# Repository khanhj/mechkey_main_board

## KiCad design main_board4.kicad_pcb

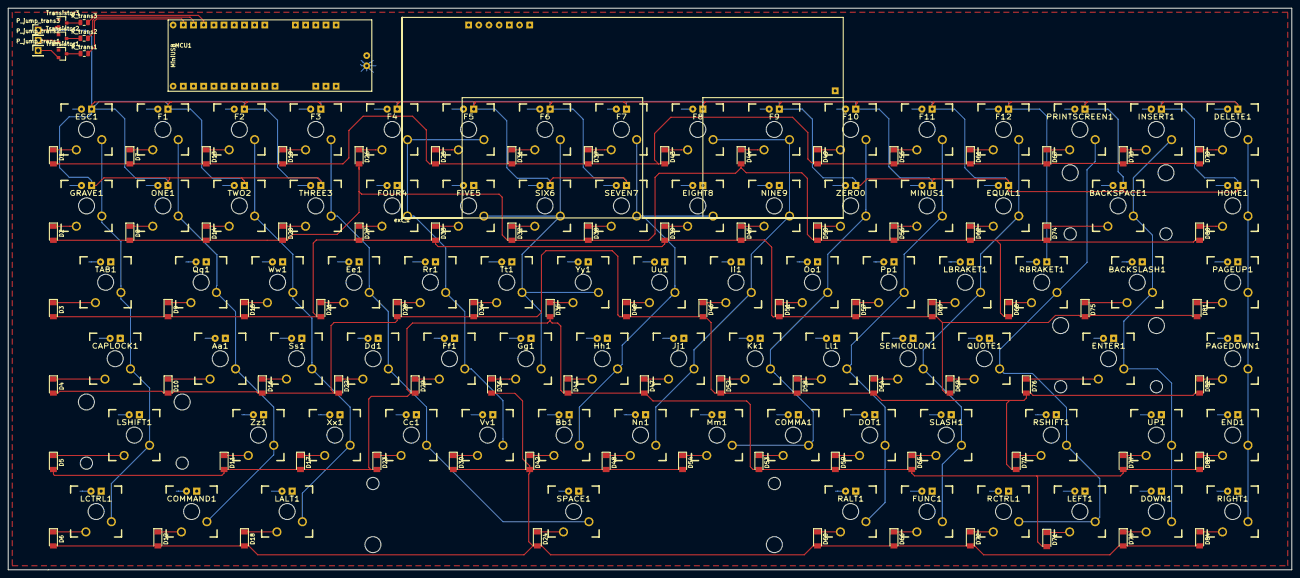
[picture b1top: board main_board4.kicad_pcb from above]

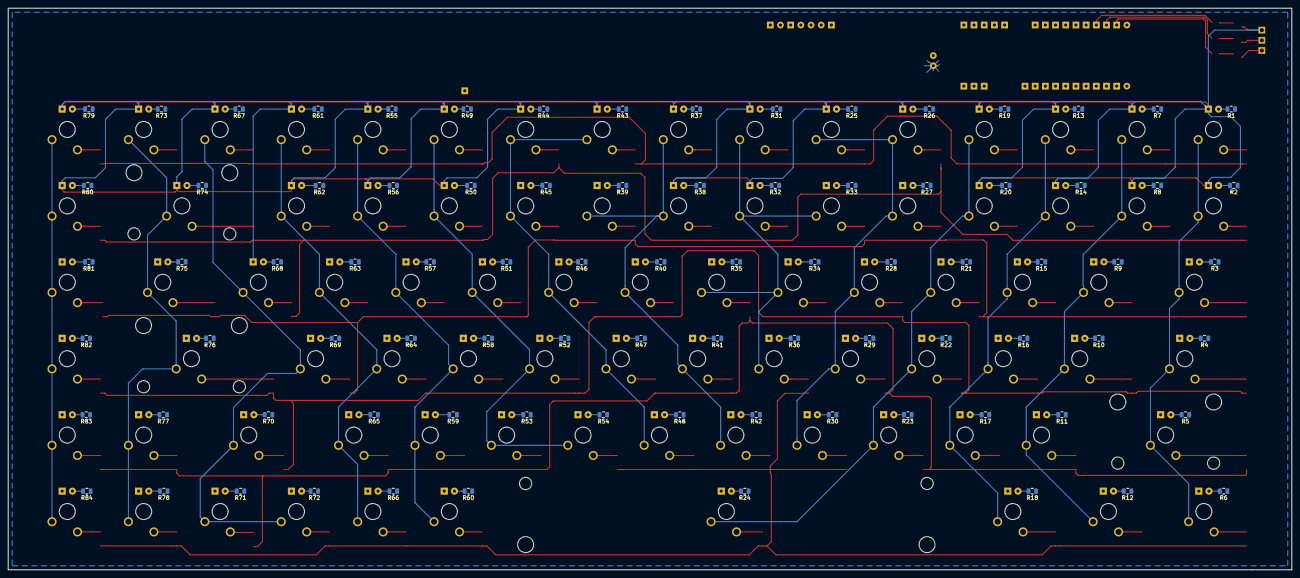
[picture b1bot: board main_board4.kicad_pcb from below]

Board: 2 copper layers, 320.0 x 140.0 mm, 263 parts (84 on the bottom side), 203 nets.

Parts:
Aa1: SWITCH_PUSH; CHERRY_PCB_100H
BACKSLASH1: SWITCH_PUSH; CHERRY_PCB_150H
BACKSPACE1: SWITCH_PUSH; CHERRY_PCB_200H
Bb1: SWITCH_PUSH; CHERRY_PCB_100H
CAPLOCK1: SWITCH_PUSH; CHERRY_PCB_175H
COMMA1: SWITCH_PUSH; CHERRY_PCB_100H
COMMAND1: SWITCH_PUSH; CHERRY_PCB_125H
Cc1: SWITCH_PUSH; CHERRY_PCB_100H
D1, D2, D3, D4, D5, D6, D7, D8, D9, D10, D11, D12, D13, D14, D15, D16, D17, D18, D19, D20, D21, D22, D23, D24, D25, D26, D27, D28, D29, D30, D31, D32, D33, D34, D35, D36, D37, D38, D39, D40, D41, D42, D43, D44, D45, D46, D47, D48, D49, D50, D51, D52, D53, D54, D55, D56, D57, D58, D59, D60, D61, D62, D63, D64, D65, D66, D67, D68, D69, D70, D71, D72, D73, D74, D75, D76, D77, D78, D79, D80, D81, D82, D83, D84: DIODE; D_MiniMELFr
DELETE1: SWITCH_PUSH; CHERRY_PCB_100H
DOT1: SWITCH_PUSH; CHERRY_PCB_100H
DOWN1: SWITCH_PUSH; CHERRY_PCB_100H
Dd1: SWITCH_PUSH; CHERRY_PCB_100H
EIGHT8: SWITCH_PUSH; CHERRY_PCB_100H
END1: SWITCH_PUSH; CHERRY_PCB_100H
ENTER1: SWITCH_PUSH; CHERRY_PCB_225H
EQUAL1: SWITCH_PUSH; CHERRY_PCB_100H
ESC1: SWITCH_PUSH; CHERRY_PCB_100H
Ee1: SWITCH_PUSH; CHERRY_PCB_100H
F1, F2, F3, F4, F5, F6, F7, F8, F9, F10, F11, F12: SWITCH_PUSH; CHERRY_PCB_100H
FIVE5: SWITCH_PUSH; CHERRY_PCB_100H
FOUR4: SWITCH_PUSH; CHERRY_PCB_100H
FUNC1: SWITCH_PUSH; CHERRY_PCB_100H
Ff1: SWITCH_PUSH; CHERRY_PCB_100H
GRAVE1: SWITCH_PUSH; CHERRY_PCB_100H
Gg1: SWITCH_PUSH; CHERRY_PCB_100H
HOME1: SWITCH_PUSH; CHERRY_PCB_100H
Hh1: SWITCH_PUSH; CHERRY_PCB_100H
INSERT1: SWITCH_PUSH; CHERRY_PCB_100H
Ii1: SWITCH_PUSH; CHERRY_PCB_100H
Jj1: SWITCH_PUSH; CHERRY_PCB_100H
Kk1: SWITCH_PUSH; CHERRY_PCB_100H
LALT1: SWITCH_PUSH; CHERRY_PCB_125H
LBRAKET1: SWITCH_PUSH; CHERRY_PCB_100H
LCTRL1: SWITCH_PUSH; CHERRY_PCB_125H
LEFT1: SWITCH_PUSH; CHERRY_PCB_100H
LSHIFT1: SWITCH_PUSH; CHERRY_PCB_225H
Ll1: SWITCH_PUSH; CHERRY_PCB_100H
MCU1: Teensy2.0++; Teensy2.0++_footprint_assigned
MINUS1: SWITCH_PUSH; CHERRY_PCB_100H
Mm1: SWITCH_PUSH; CHERRY_PCB_100H
NINE9: SWITCH_PUSH; CHERRY_PCB_100H
Nn1: SWITCH_PUSH; CHERRY_PCB_100H
ONE1: SWITCH_PUSH; CHERRY_PCB_100H
Oo1: SWITCH_PUSH; CHERRY_PCB_100H
PAGEDOWN1: SWITCH_PUSH; CHERRY_PCB_100H
PAGEUP1: SWITCH_PUSH; CHERRY_PCB_100H
PRINTSCREEN1: SWITCH_PUSH; CHERRY_PCB_100H
P_jump_trans1, P_jump_trans2, P_jump_trans3: CONN_01X01; PinHeader_1x01_P2.54mm_Vertical
Pp1: SWITCH_PUSH; CHERRY_PCB_100H
QUOTE1: SWITCH_PUSH; CHERRY_PCB_100H
Qq1: SWITCH_PUSH; CHERRY_PCB_100H
R1, R2, R3, R4, R5, R6, R7, R8, R9, R10, R11, R12, R13, R14, R15, R16, R17, R18, R19, R20, R21, R22, R23, R24, R25, R26, R27, R28, R29, R30, R31, R32, R33, R34, R35, R36, R37, R38, R39, R40, R41, R42, R43, R44, R45, R46, R47, R48, R49, R50, R51, R52, R53, R54, R55, R56, R57, R58, R59, R60, R61, R62, R63, R64, R65, R66, R67, R68, R69, R70, R71, R72, R73, R74, R75, R76, R77, R78, R79, R80, R81, R82, R83, R84: R; R_0805_2012Metric
RALT1: SWITCH_PUSH; CHERRY_PCB_100H
RBRAKET1: SWITCH_PUSH; CHERRY_PCB_100H
RCTRL1: SWITCH_PUSH; CHERRY_PCB_100H
RIGHT1: SWITCH_PUSH; CHERRY_PCB_100H
RSHIFT1: SWITCH_PUSH; CHERRY_PCB_175H
R_trans1, R_trans2, R_trans3: R; R_0805_2012Metric
Rr1: SWITCH_PUSH; CHERRY_PCB_100H
SEMICOLON1: SWITCH_PUSH; CHERRY_PCB_100H
SEVEN7: SWITCH_PUSH; CHERRY_PCB_100H
SIX6: SWITCH_PUSH; CHERRY_PCB_100H
SLASH1: SWITCH_PUSH; CHERRY_PCB_100H
SPACE1: SWITCH_PUSH; CHERRY_PCB_625H
Ss1: SWITCH_PUSH; CHERRY_PCB_100H
TAB1: SWITCH_PUSH; CHERRY_PCB_150H
THREE3: SWITCH_PUSH; CHERRY_PCB_100H
TWO2: SWITCH_PUSH; CHERRY_PCB_100H
Transistor1, Transistor2, Transistor3: 2SC1815; SOT-23
Tt1: SWITCH_PUSH; CHERRY_PCB_100H
UP1: SWITCH_PUSH; CHERRY_PCB_100H
Uu1: SWITCH_PUSH; CHERRY_PCB_100H
Vv1: SWITCH_PUSH; CHERRY_PCB_100H
Ww1: SWITCH_PUSH; CHERRY_PCB_100H
Xx1: SWITCH_PUSH; CHERRY_PCB_100H
Yy1: SWITCH_PUSH; CHERRY_PCB_100H
ZERO0: SWITCH_PUSH; CHERRY_PCB_100H
Zz1: SWITCH_PUSH; CHERRY_PCB_100H
ext_1: ext_module_comp; ext_module_footprint

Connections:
unnamed: Aa1.1, D10.1
unnamed: Aa1.2, COMMAND1.2, F1.2, MCU1.3, ONE1.2, Qq1.2, Zz1.2
unnamed: Aa1.3, R10.2
unnamed: Aa1.4, BACKSLASH1.4, CAPLOCK1.4, Dd1.4, EIGHT8.4, ENTER1.4, Ee1.4, FIVE5.4, FOUR4.4, Ii1.4, Kk1.4, LBRAKET1.4, Ll1.4, NINE9.4, Oo1.4, PAGEDOWN1.4, PAGEUP1.4, P_jump_trans2.1, Pp1.4, QUOTE1.4, Qq1.4, RSHIFT1.4, Rr1.4, SEMICOLON1.4, Ss1.4, TAB1.4, Transistor2.2, Tt1.4, Uu1.4, Ww1.4
unnamed: BACKSLASH1.1, D75.1
unnamed: BACKSLASH1.2, BACKSPACE1.2, DOWN1.2, ENTER1.2, INSERT1.2, MCU1.22, UP1.2
unnamed: BACKSLASH1.3, R75.2
unnamed: BACKSPACE1.1, D74.1
unnamed: BACKSPACE1.3, R74.2
unnamed: BACKSPACE1.4, DELETE1.4, EQUAL1.4, ESC1.4, F1.4, F2.4, F3.4, F4.4, F5.4, F6.4, F7.4, F8.4, F9.4, F10.4, F11.4, F12.4, GRAVE1.4, HOME1.4, INSERT1.4, MINUS1.4, ONE1.4, PRINTSCREEN1.4, P_jump_trans3.1, RBRAKET1.4, SEVEN7.4, SIX6.4, THREE3.4, TWO2.4, Transistor3.2, ZERO0.4
unnamed: Bb1.1, D42.1
unnamed: Bb1.2, EIGHT8.2, F7.2, Hh1.2, MCU1.8, SEVEN7.2, Uu1.2
unnamed: Bb1.3, R42.2
unnamed: Bb1.4, COMMA1.4, COMMAND1.4, Cc1.4, DOT1.4, DOWN1.4, END1.4, FUNC1.4, Ff1.4, Gg1.4, Hh1.4, Jj1.4, LALT1.4, LCTRL1.4, LEFT1.4, LSHIFT1.4, Mm1.4, Nn1.4, P_jump_trans1.1, RALT1.4, RCTRL1.4, RIGHT1.4, SLASH1.4, SPACE1.4, Transistor1.2, UP1.4, Vv1.4, Xx1.4, Yy1.4, Zz1.4
unnamed: CAPLOCK1.1, D4.1
unnamed: CAPLOCK1.2, ESC1.2, GRAVE1.2, LCTRL1.2, LSHIFT1.2, MCU1.2, TAB1.2
unnamed: CAPLOCK1.3, R4.2
unnamed: COMMA1.1, D53.1
unnamed: COMMA1.2, F10.2, Kk1.2, MCU1.18, Mm1.2, Oo1.2, ZERO0.2
unnamed: COMMA1.3, R53.2
unnamed: COMMAND1.1, D12.1
unnamed: COMMAND1.3, R12.2
unnamed: Cc1.1, D23.1
unnamed: Cc1.2, Dd1.2, Ee1.2, F3.2, MCU1.5, SPACE1.2, THREE3.2
unnamed: Cc1.3, R23.2
unnamed: D1.1, ESC1.1
unnamed: D1.2, D7.2, D13.2, D19.2, D25.2, D31.2, D37.2, D43.2, D49.2, D55.2, D61.2, D67.2, D73.2, D79.2, MCU1.12
unnamed: D2.1, GRAVE1.1
unnamed: D3.1, TAB1.1
unnamed: D5.1, LSHIFT1.1
unnamed: D6.1, LCTRL1.1
unnamed: D7.1, F1.1
unnamed: D8.1, ONE1.1
unnamed: D9.1, Qq1.1
unnamed: D4.2, D10.2, D16.2, D22.2, D28.2, D34.2, D40.2, D46.2, D52.2, D58.2, D64.2, D70.2, D76.2, D82.2, MCU1.42
unnamed: D11.1, Zz1.1
unnamed: D5.2, D11.2, D17.2, D23.2, D29.2, D35.2, D41.2, D47.2, D53.2, D59.2, D65.2, D71.2, D77.2, D83.2, MCU1.41
unnamed: D6.2, D12.2, D18.2, D24.2, D30.2, D36.2, D42.2, D48.2, D54.2, D60.2, D66.2, D72.2, D78.2, D84.2, MCU1.40
unnamed: D13.1, F2.1
unnamed: D14.1, TWO2.1
unnamed: D2.2, D8.2, D14.2, D20.2, D26.2, D32.2, D38.2, D44.2, D50.2, D56.2, D62.2, D68.2, D74.2, D80.2, MCU1.13
unnamed: D15.1, Ww1.1
unnamed: D3.2, D9.2, D15.2, D21.2, D27.2, D33.2, D39.2, D45.2, D51.2, D57.2, D63.2, D69.2, D75.2, D81.2, MCU1.14
unnamed: D16.1, Ss1.1
unnamed: D17.1, Xx1.1
unnamed: D18.1, LALT1.1
unnamed: D19.1, F3.1
unnamed: D20.1, THREE3.1
unnamed: D21.1, Ee1.1
unnamed: D22.1, Dd1.1
unnamed: D24.1, SPACE1.1
unnamed: D25.1, F5.1
unnamed: D26.1, F4.1
unnamed: D27.1, FOUR4.1
unnamed: D28.1, Rr1.1
unnamed: D29.1, Ff1.1
unnamed: D30.1, Vv1.1
unnamed: D31.1, F6.1
unnamed: D32.1, SIX6.1
unnamed: D33.1, FIVE5.1
unnamed: D34.1, Tt1.1
unnamed: D35.1, Yy1.1
unnamed: D36.1, Gg1.1
unnamed: D37.1, F7.1
unnamed: D38.1, SEVEN7.1
unnamed: D39.1, EIGHT8.1
unnamed: D40.1, Uu1.1
unnamed: D41.1, Hh1.1
unnamed: D43.1, F8.1
unnamed: D44.1, F9.1
unnamed: D45.1, NINE9.1
unnamed: D46.1, Ii1.1
unnamed: D47.1, Jj1.1
unnamed: D48.1, Nn1.1
unnamed: D49.1, F10.1
unnamed: D50.1, ZERO0.1
unnamed: D51.1, Oo1.1
unnamed: D52.1, Kk1.1
unnamed: D54.1, Mm1.1
unnamed: D55.1, F11.1
unnamed: D56.1, MINUS1.1
unnamed: D57.1, Pp1.1
unnamed: D58.1, Ll1.1
unnamed: D59.1, DOT1.1
unnamed: D60.1, RALT1.1
unnamed: D61.1, F12.1
unnamed: D62.1, EQUAL1.1
unnamed: D63.1, LBRAKET1.1
unnamed: D64.1, SEMICOLON1.1
unnamed: D65.1, SLASH1.1
unnamed: D66.1, FUNC1.1
unnamed: D67.1, PRINTSCREEN1.1
unnamed: D68.1, RBRAKET1.1
unnamed: D69.1, QUOTE1.1
unnamed: D70.1, RSHIFT1.1
unnamed: D71.1, LEFT1.1
unnamed: D72.1, RCTRL1.1
unnamed: D73.1, INSERT1.1
unnamed: D76.1, ENTER1.1
unnamed: D77.1, UP1.1
unnamed: D78.1, DOWN1.1
unnamed: D79.1, DELETE1.1
unnamed: D80.1, HOME1.1
unnamed: D81.1, PAGEUP1.1
unnamed: D82.1, PAGEDOWN1.1
unnamed: D83.1, END1.1
unnamed: D84.1, RIGHT1.1
unnamed: DELETE1.2, END1.2, HOME1.2, MCU1.23, PAGEDOWN1.2, PAGEUP1.2, RIGHT1.2
unnamed: DELETE1.3, R79.2
unnamed: DOT1.2, F11.2, Ll1.2, MCU1.19, MINUS1.2, Pp1.2, RALT1.2
unnamed: DOT1.3, R59.2
unnamed: DOWN1.3, R78.2
unnamed: Dd1.3, R22.2
unnamed: EIGHT8.3, R39.2
unnamed: END1.3, R83.2
unnamed: ENTER1.3, R76.2
unnamed: EQUAL1.2, F12.2, FUNC1.2, LBRAKET1.2, MCU1.20, SEMICOLON1.2, SLASH1.2
unnamed: EQUAL1.3, R62.2
unnamed: ESC1.3, R1.2
unnamed: Ee1.3, R21.2
unnamed: F1.3, R7.2
unnamed: F2.2, LALT1.2, MCU1.4, Ss1.2, TWO2.2, Ww1.2, Xx1.2
unnamed: F2.3, R13.2
unnamed: F3.3, R19.2
unnamed: F4.2, F5.2, FOUR4.2, Ff1.2, MCU1.6, Rr1.2, Vv1.2
unnamed: F4.3, R26.2
unnamed: F5.3, R25.2
unnamed: F6.2, FIVE5.2, Gg1.2, MCU1.7, SIX6.2, Tt1.2, Yy1.2
unnamed: F6.3, R31.2
unnamed: F7.3, R37.2
unnamed: F8.2, F9.2, Ii1.2, Jj1.2, MCU1.38, NINE9.2, Nn1.2
unnamed: F8.3, R43.2
unnamed: F9.3, R44.2
unnamed: F10.3, R49.2
unnamed: F11.3, R55.2
unnamed: F12.3, R61.2
unnamed: FIVE5.3, R33.2
unnamed: FOUR4.3, R27.2
unnamed: FUNC1.3, R66.2
unnamed: Ff1.3, R29.2
unnamed: GRAVE1.3, R2.2
unnamed: Gg1.3, R36.2
unnamed: HOME1.3, R80.2
unnamed: Hh1.3, R41.2
unnamed: INSERT1.3, R73.2
unnamed: Ii1.3, R46.2
unnamed: Jj1.3, R47.2
unnamed: Kk1.3, R52.2
unnamed: LALT1.3, R18.2
unnamed: LBRAKET1.3, R63.2
unnamed: LCTRL1.3, R6.2
unnamed: LEFT1.2, MCU1.21, PRINTSCREEN1.2, QUOTE1.2, RBRAKET1.2, RCTRL1.2, RSHIFT1.2
unnamed: LEFT1.3, R71.2
unnamed: LSHIFT1.3, R5.2
unnamed: Ll1.3, R58.2
unnamed: MCU1.0, ext_1.5
unnamed: MCU1.1, ext_1.6
unnamed: MCU1.24, R_trans3.2
unnamed: MCU1.25, R_trans2.2
unnamed: MCU1.26, R_trans1.2
unnamed: MCU1.27, ext_1.8
unnamed: MCU1.39, ext_1.7
unnamed: MCU1.46, R1.1, R2.1, R3.1, R4.1, R5.1, R6.1, R7.1, R8.1, R9.1, R10.1, R11.1, R12.1, R13.1, R14.1, R15.1, R16.1, R17.1, R18.1, R19.1, R20.1, R21.1, R22.1, R23.1, R24.1, R25.1, R26.1, R27.1, R28.1, R29.1, R30.1, R31.1, R32.1, R33.1, R34.1, R35.1, R36.1, R37.1, R38.1, R39.1, R40.1, R41.1, R42.1, R43.1, R44.1, R45.1, R46.1, R47.1, R48.1, R49.1, R50.1, R51.1, R52.1, R53.1, R54.1, R55.1, R56.1, R57.1, R58.1, R59.1, R60.1, R61.1, R62.1, R63.1, R64.1, R65.1, R66.1, R67.1, R68.1, R69.1, R70.1, R71.1, R72.1, R73.1, R74.1, R75.1, R76.1, R77.1, R78.1, R79.1, R80.1, R81.1, R82.1, R83.1, R84.1, ext_1.1
unnamed: MCU1.49, Transistor1.1, Transistor2.1, Transistor3.1, ext_1.4
unnamed: MINUS1.3, R56.2
unnamed: Mm1.3, R54.2
unnamed: NINE9.3, R45.2
unnamed: Nn1.3, R48.2
unnamed: ONE1.3, R8.2
unnamed: Oo1.3, R51.2
unnamed: PAGEDOWN1.3, R82.2
unnamed: PAGEUP1.3, R81.2
unnamed: PRINTSCREEN1.3, R67.2
unnamed: Pp1.3, R57.2
unnamed: QUOTE1.3, R69.2
unnamed: Qq1.3, R9.2
unnamed: R3.2, TAB1.3
unnamed: R11.2, Zz1.3
unnamed: R14.2, TWO2.3
unnamed: R15.2, Ww1.3
unnamed: R16.2, Ss1.3
unnamed: R17.2, Xx1.3
unnamed: R20.2, THREE3.3
unnamed: R24.2, SPACE1.3
unnamed: R28.2, Rr1.3
unnamed: R30.2, Vv1.3
unnamed: R32.2, SIX6.3
unnamed: R34.2, Tt1.3
unnamed: R35.2, Yy1.3
unnamed: R38.2, SEVEN7.3
unnamed: R40.2, Uu1.3
unnamed: R50.2, ZERO0.3
unnamed: R60.2, RALT1.3
unnamed: R64.2, SEMICOLON1.3
unnamed: R65.2, SLASH1.3
unnamed: R68.2, RBRAKET1.3
unnamed: R70.2, RSHIFT1.3
unnamed: R72.2, RCTRL1.3
unnamed: R77.2, UP1.3
unnamed: R84.2, RIGHT1.3
unnamed: R_trans1.1, Transistor1.3
unnamed: R_trans2.1, Transistor2.3
unnamed: R_trans3.1, Transistor3.3

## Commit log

2018-10-18 commit lib
2018-10-18 1st ver
2018-10-18 update footprint
2018-10-18 add footprint
2018-10-19 mapping
2018-10-21 big chang
2018-10-26 working on pcb layout
2018-10-29 diode placement
2018-11-01 update pin out
2018-11-01 update pcb
2018-11-05 almost
2018-11-10 update led1
2018-11-11 update pinout, flip teensy
